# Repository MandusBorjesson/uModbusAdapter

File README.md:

# uModbusAdapter
A tiny USB-C to RS-485 adapter with headers for both RS-485 and UART signals.

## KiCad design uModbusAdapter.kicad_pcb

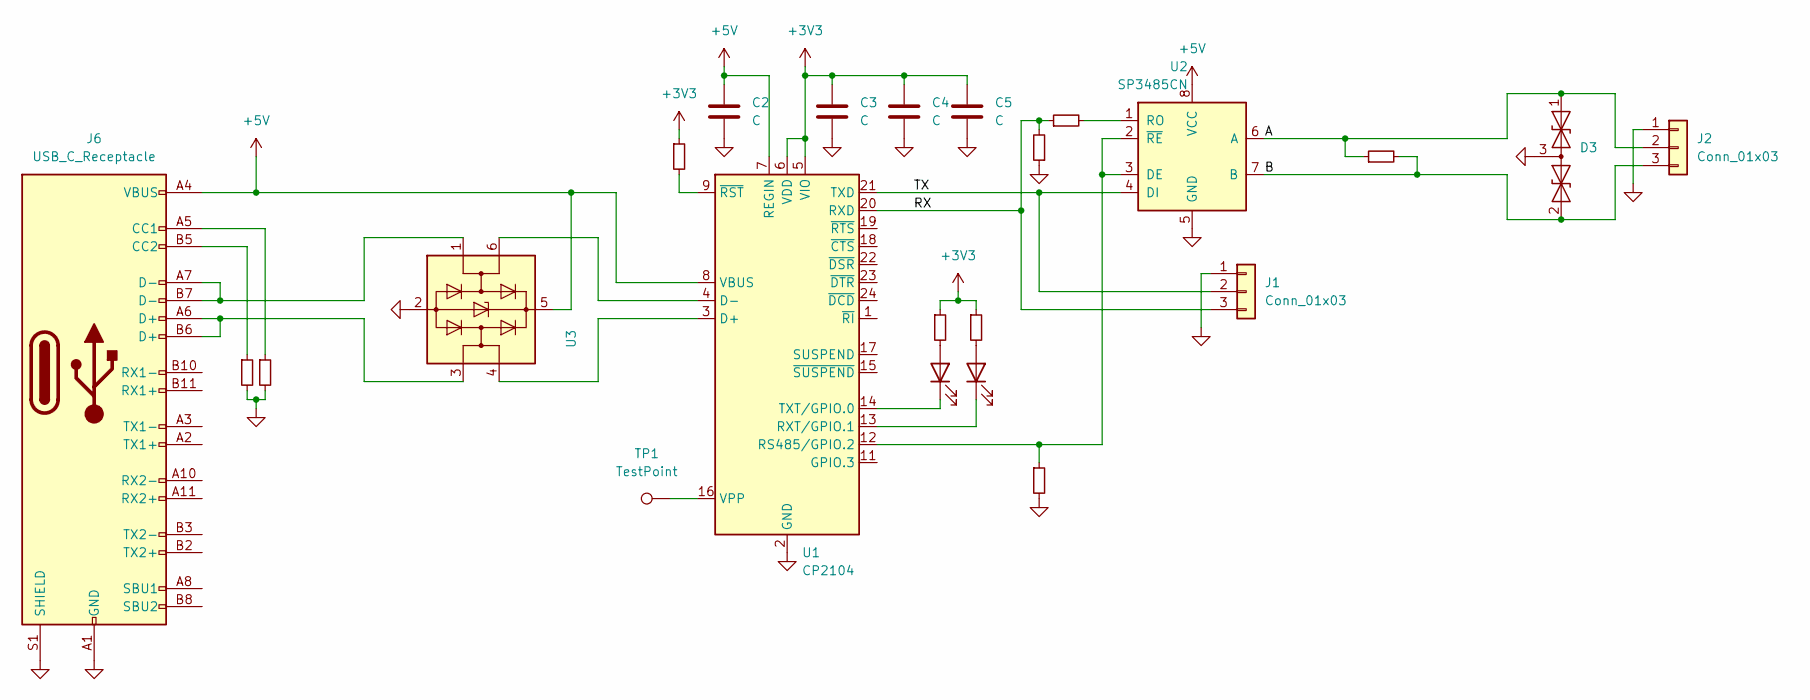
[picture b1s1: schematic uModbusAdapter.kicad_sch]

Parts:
C2, C3, C4, C5: C; C_0603_1608Metric
D1, D2: LED; LED_0805_2012Metric
D3: SM712_SOT23; SOT-23
J1, J2: Conn_01x03; JST_EH_B3B-EH-A_1x03_P2.50mm_Vertical
J6: USB_C_Receptacle; USB_C_Receptacle_HRO_TYPE-C-31-M-12
R1, R2, R3, R4, R5, R6, R7, R8, R9: R_Small; R_0603_1608Metric
TP1: TestPoint; TestPoint_Pad_1.5x1.5mm
U1: CP2104; QFN-24-1EP_4x4mm_P0.5mm_EP2.6x2.6mm
U2: SP3485CN; SOIC-8_3.9x4.9mm_P1.27mm
U3: USBLC6-2SC6; SOT-23-6

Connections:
+3V3: C3.1, C4.1, C5.1, R1.1, R2.1, R3.1, U1.5 (VIO), U1.6 (VDD)
+5V: C2.1, J6.A4 (VBUS), J6.A9 (VBUS), J6.B4 (VBUS), J6.B9 (VBUS), U1.7 (REGIN), U1.8 (VBUS), U2.8 (VCC), U3.5 (VBUS)
/A: D3.1 (A1), J2.2, R4.1, U2.6 (A)
/B: D3.2 (A2), J2.3, R4.2, U2.7 (B)
/RX: J1.3, R8.2, R9.1, U1.20 (RXD)
/TX: J1.2, U1.21 (TXD), U2.4 (DI)
GND: C2.2, C3.2, C4.2, C5.2, D3.3 (common), J1.1, J2.1, J6.A1 (GND), J6.A12 (GND), J6.B1 (GND), J6.B12 (GND), J6.S1 (SHIELD), R5.2, R6.2, R7.2, R8.1, U1.2 (GND), U1.25 (GND), U2.5 (GND), U3.2 (GND)
unnamed: D1.1 (K), U1.14 (TXT/GPIO.0)
unnamed: D1.2 (A), R2.2
unnamed: D2.1 (K), U1.13 (RXT/GPIO.1)
unnamed: D2.2 (A), R3.2
unnamed: J6.A5 (CC1), R6.1
unnamed: J6.A6 (D+), J6.B6 (D+), U3.3 (I/O2)
unnamed: J6.A7 (D-), J6.B7 (D-), U3.1 (I/O1)
unnamed: J6.B5 (CC2), R5.1
unnamed: R1.2, U1.9 (~RST)
unnamed: R7.1, U1.12 (RS485/GPIO.2), U2.2 (~RE), U2.3 (DE)
unnamed: TP1.1, U1.16 (VPP)
unnamed: U1.3 (D+), U3.4 (I/O2)
unnamed: U1.4 (D-), U3.6 (I/O1)
unnamed: R9.2, U2.1 (RO)

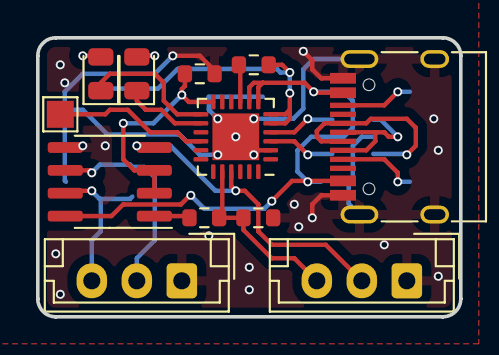
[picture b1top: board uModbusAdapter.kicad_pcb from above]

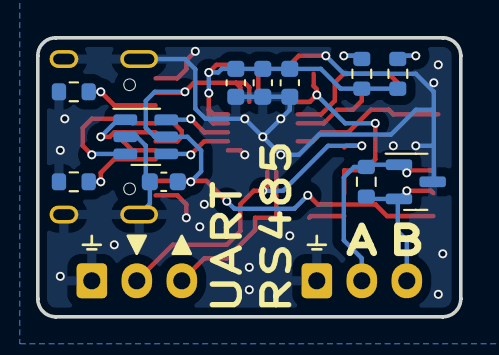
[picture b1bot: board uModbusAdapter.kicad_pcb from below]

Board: 2 copper layers, 23.5 x 15.5 mm, 23 parts (11 on the bottom side), 21 nets.

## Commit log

2024-09-04 Version 1
